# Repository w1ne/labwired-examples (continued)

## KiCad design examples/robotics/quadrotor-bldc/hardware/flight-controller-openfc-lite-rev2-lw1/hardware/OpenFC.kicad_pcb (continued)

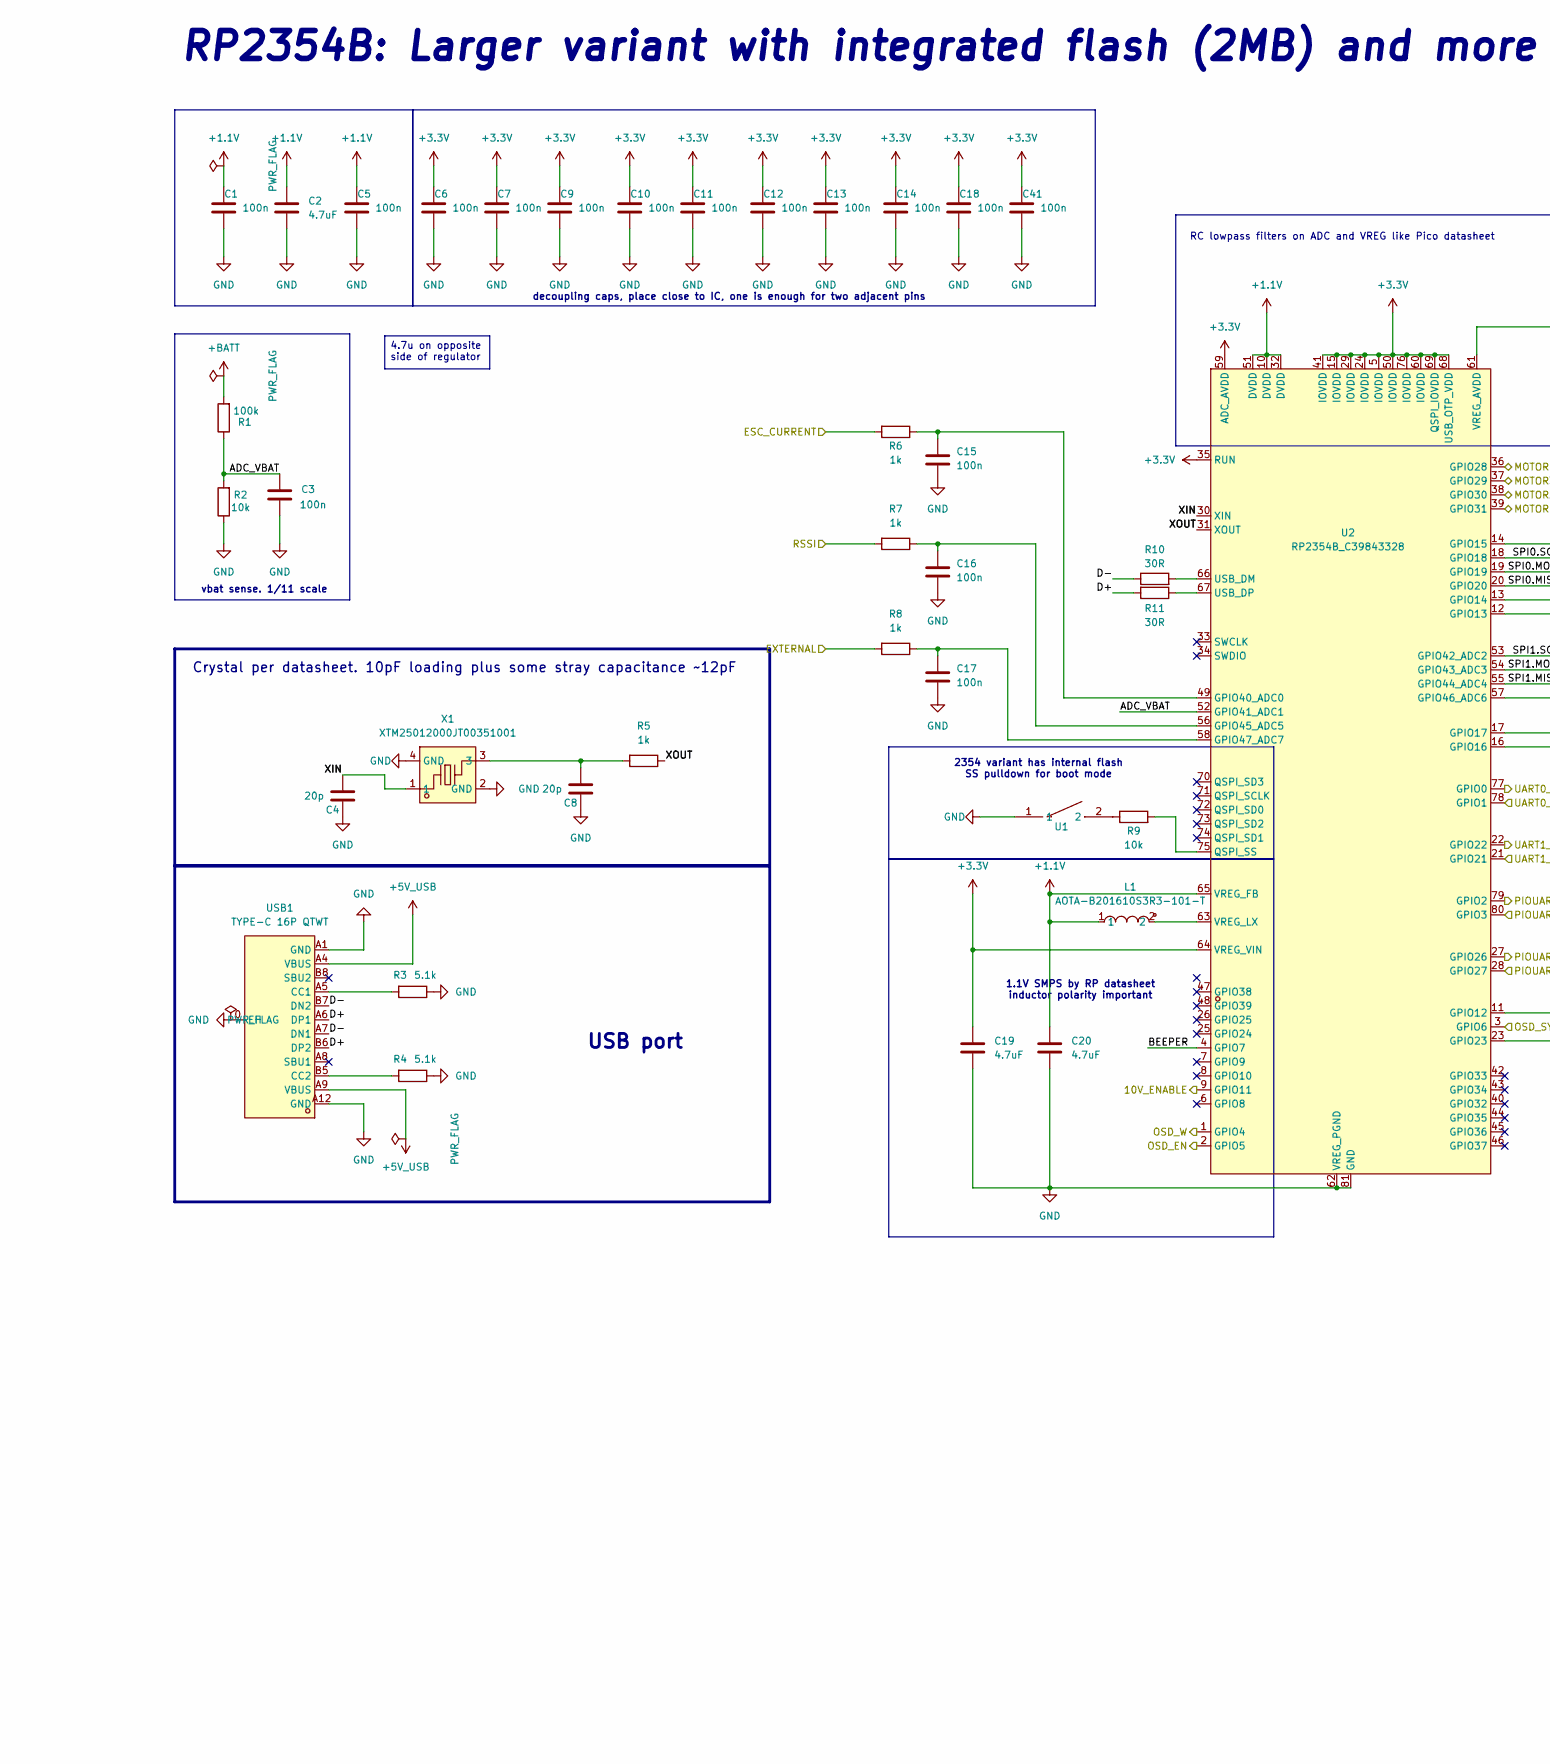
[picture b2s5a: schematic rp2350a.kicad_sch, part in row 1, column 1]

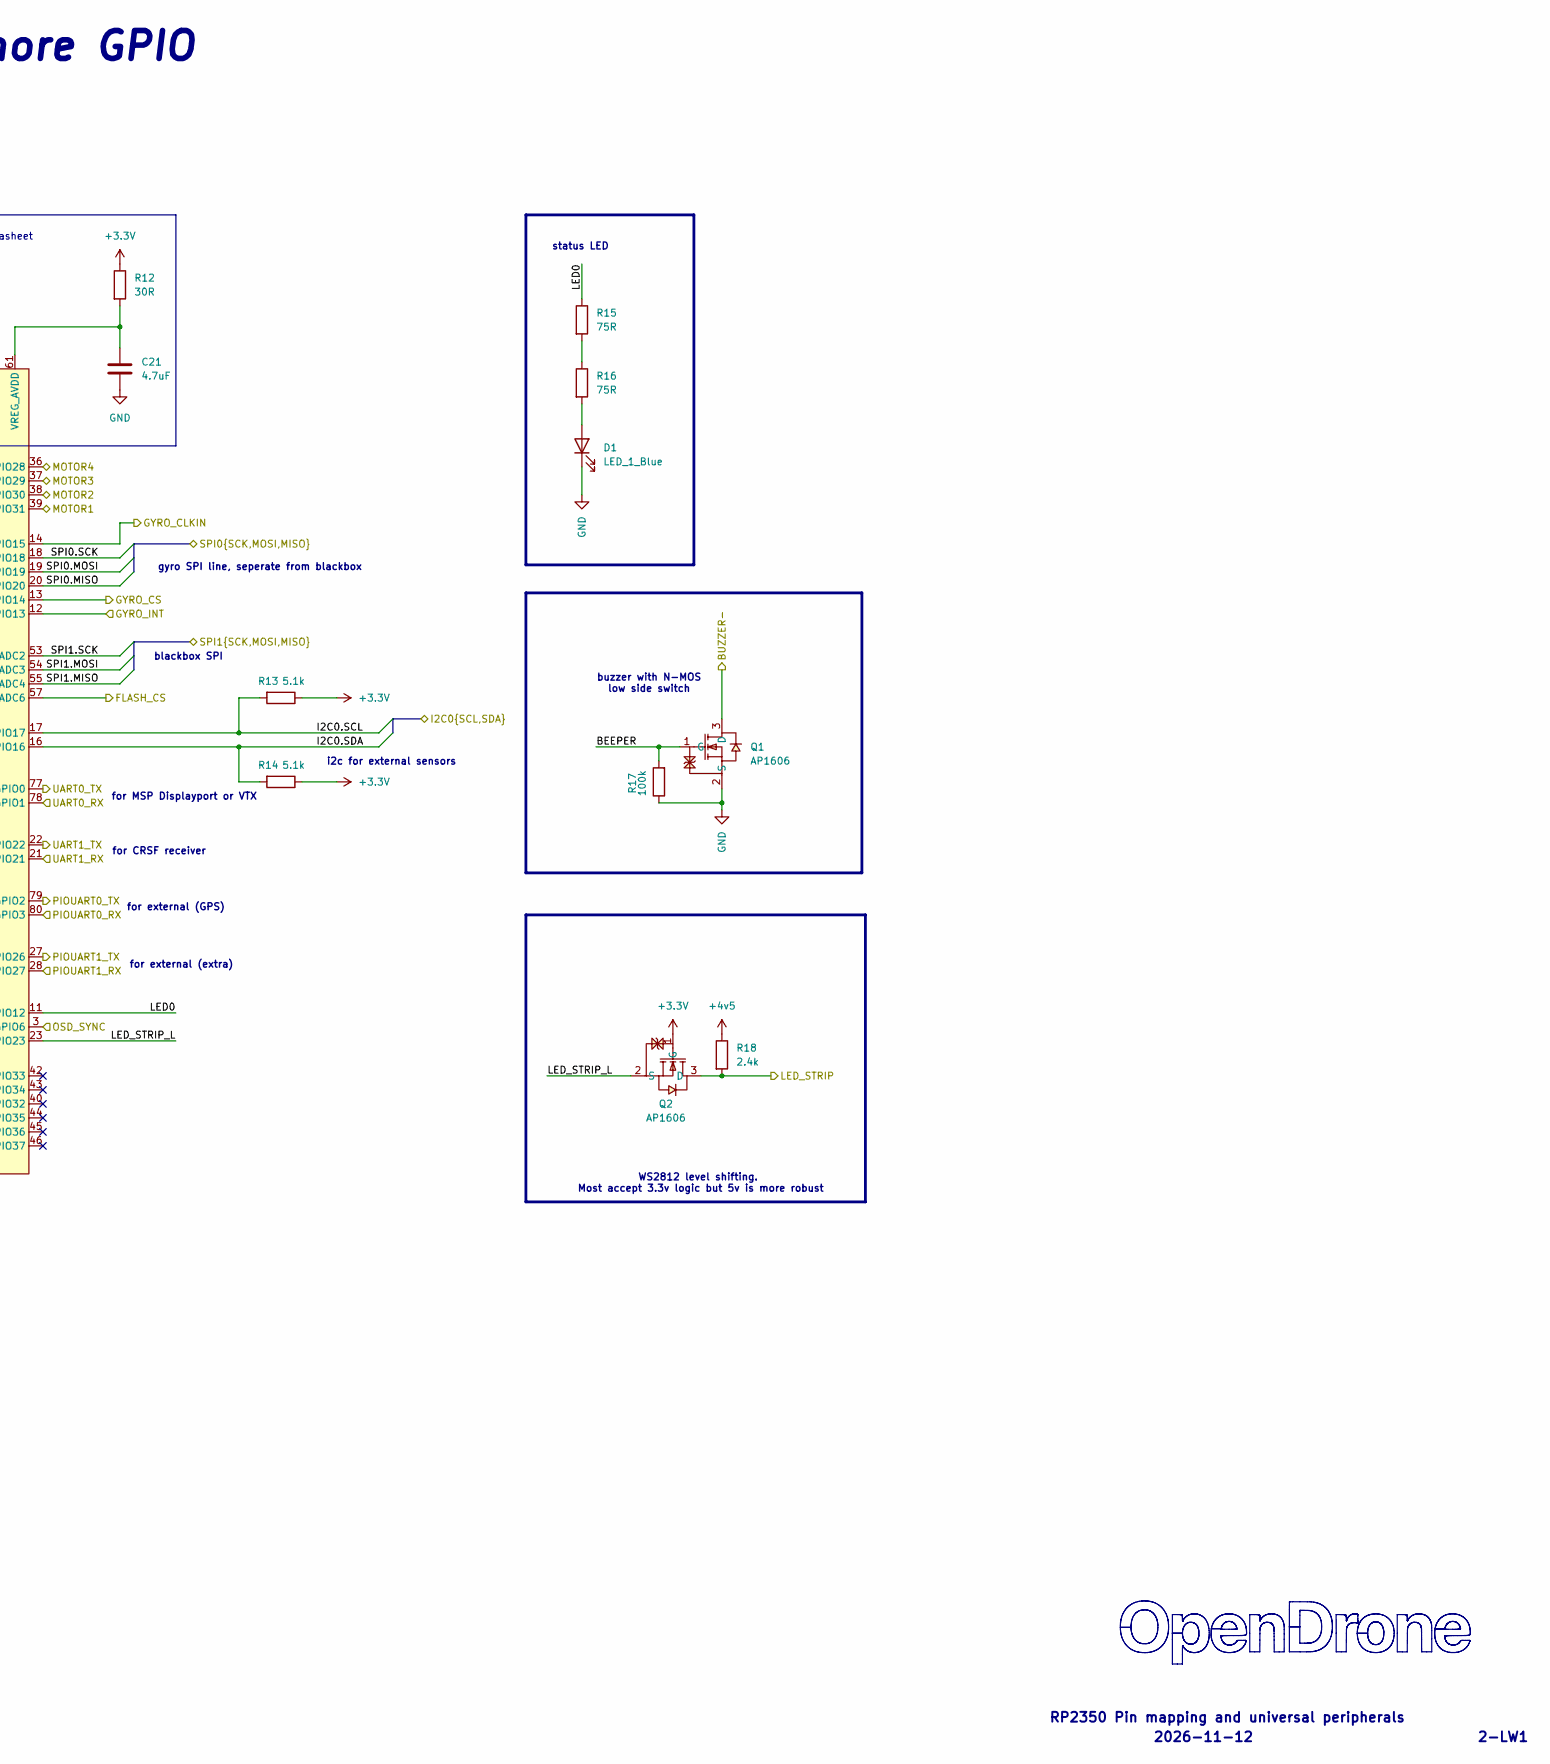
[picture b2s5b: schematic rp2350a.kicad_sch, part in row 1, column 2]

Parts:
C1, C3, C5, C6, C7, C9, C10, C11, C12, C13, C14, C15, C16, C17, C18, C41: 100n; C_0201_0603Metric; MPN GRM033R61E104KE14D; LCSC C76939
C2, C19, C20, C21: 4.7uF; C_0402_1005Metric; MPN CL05A475MP5NRNC; LCSC C23733
C4, C8: 20p; C_0201_0603Metric; MPN GRM0335C1H200JA01D; LCSC C76923
D1: LED_1_Blue; LED_0402_1005Metric; MPN XL-1005UBC; LCSC C22355736
L1: AOTA-B201610S3R3-101-T; IND-SMD_L2.0-W1.6_AOTA-B201610S3R3-101-T; MPN AOTA-B201610S3R3-101-T; LCSC C42411119
Q1, Q2: AP1606; DFN-3L_L1.0-W0.6-P0.65-BR; MPN AP1606; LCSC C2849580
R1, R17: 100k; R_0201_0603Metric; MPN 0201WMF1003TEE; LCSC C270364
R2, R9: 10k; R_0201_0603Metric; MPN RC0201FR-0710KL; LCSC C106225
R3, R4, R13, R14: 5.1k; R_0201_0603Metric; MPN 0201WMF5101TEE; LCSC C270344
R5, R6, R7, R8: 1k; R_0201_0603Metric; MPN 0201WMF1001TEE; LCSC C270365
R10, R11, R12: 30R; R_0201_0603Metric; MPN NQ01WMJ0300TEE; LCSC C778391
R15, R16: 75R; R_0201_0603Metric; MPN RC0201FR-0775RL; LCSC C274878
R18: 2.4k; R_0201_0603Metric; MPN RTT012401FTH; LCSC C166281
U1: TS2306A 240GF MSM 9_C2976675; SW-SMD_4P-L3.0-W2.0-P0.85-LS3.5; MPN TS2306A 240gf MSM 9; LCSC C2976675
U2: RP2354B_C39843328; QFN-80_L10.0-W10.0-P0.40-TL-EP3.4; MPN RP2354B; LCSC C39843328
USB1: TYPE-C 16P QTWT; USB-TYPE-C-SMD_TYPE-C-16P-QTWT; MPN TYPE-C 16P QTWT; LCSC C5187472
X1: XTM25012000JT00351001; CRYSTAL-SMD_4P-L2.5-W2.0-BL-A; MPN XTM25012000JT00351001; LCSC C37635340

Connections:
+1.1V: C1.1, C2.1, C5.1, C20.1, L1.1, U2.10 (DVDD), U2.32 (DVDD), U2.51 (DVDD), U2.65 (VREG_FB)
+3.3V: C6.1, C7.1, C9.1, C10.1, C11.1, C12.1, C13.1, C14.1, C18.1, C19.1, C41.1, Q2.1 (G), R12.1, R13.1, R14.1, U2.5 (IOVDD), U2.15 (IOVDD), U2.24 (IOVDD), U2.29 (IOVDD), U2.35 (RUN), U2.41 (IOVDD), U2.50 (IOVDD), U2.59 (ADC_AVDD), U2.60 (IOVDD), U2.64 (VREG_VIN), U2.68 (USB_OTP_VDD), U2.69 (QSPI_IOVDD), U2.76 (IOVDD); also elsewhere on the board
+4v5: R18.1; also elsewhere on the board
+5V_USB: USB1.A4 (VBUS), USB1.A9 (VBUS); also elsewhere on the board
+BATT: R1.2; also elsewhere on the board
/BLACKBOX/FLASH_CS: U2.57 (GPIO46_ADC6); also elsewhere on the board
/BLACKBOX/SPI1.MISO: U2.55 (GPIO44_ADC4); also elsewhere on the board
/BLACKBOX/SPI1.MOSI: U2.54 (GPIO43_ADC3); also elsewhere on the board
/BLACKBOX/SPI1.SCK: U2.53 (GPIO42_ADC2); also elsewhere on the board
/IMU/CLKIN: U2.14 (GPIO15); also elsewhere on the board
/IMU/CS: U2.13 (GPIO14); also elsewhere on the board
/IMU/GYRO_INT: U2.12 (GPIO13); also elsewhere on the board
/IMU/SPI0.MISO: U2.20 (GPIO20); also elsewhere on the board
/IMU/SPI0.MOSI: U2.19 (GPIO19); also elsewhere on the board
/IMU/SPI0.SCK: U2.18 (GPIO18); also elsewhere on the board
/OSD/OSD_EN: U2.2 (GPIO5); also elsewhere on the board
/OSD/OSD_SYNC: U2.3 (GPIO6); also elsewhere on the board
/OSD/OSD_W: U2.1 (GPIO4); also elsewhere on the board
/PADS/ADC2: R8.2; also elsewhere on the board
/PADS/BUZZER-: Q1.3 (D); also elsewhere on the board
/PADS/CURRENT: R6.2; also elsewhere on the board
/PADS/I2C0.SCL: R13.2, U2.17 (GPIO17); also elsewhere on the board
/PADS/I2C0.SDA: R14.2, U2.16 (GPIO16); also elsewhere on the board
/PADS/LED_STRIP: Q2.3 (D), R18.2; also elsewhere on the board
/PADS/M1: U2.39 (GPIO31); also elsewhere on the board
/PADS/M2: U2.38 (GPIO30); also elsewhere on the board
/PADS/M3: U2.37 (GPIO29); also elsewhere on the board
/PADS/M4: U2.36 (GPIO28); also elsewhere on the board
/PADS/PIOUART0_RX: U2.80 (GPIO3); also elsewhere on the board
/PADS/PIOUART0_TX: U2.79 (GPIO2); also elsewhere on the board
/PADS/PIOUART1_RX: U2.28 (GPIO27); also elsewhere on the board
/PADS/PIOUART1_TX: U2.27 (GPIO26); also elsewhere on the board
/PADS/RSSI: R7.2; also elsewhere on the board
/PADS/UART0_RX: U2.78 (GPIO1); also elsewhere on the board
/PADS/UART0_TX: U2.77 (GPIO0); also elsewhere on the board
/PADS/UART1_RX: U2.21 (GPIO21); also elsewhere on the board
/PADS/UART1_TX: U2.22 (GPIO22); also elsewhere on the board
/POWER/10V_ENABLE: U2.9 (GPIO11); also elsewhere on the board
/RP2350A/ADC_VBAT: C3.2, R1.1, R2.2, U2.52 (GPIO41_ADC1)
/RP2350A/BEEPER: Q1.1 (G), R17.2, U2.4 (GPIO7)
/RP2350A/D+: R11.2, USB1.A6 (DP1), USB1.B6 (DP2)
/RP2350A/D-: R10.1, USB1.A7 (DN1), USB1.B7 (DN2)
/RP2350A/LED0: R15.1, U2.11 (GPIO12)
/RP2350A/LED_STRIP_L: Q2.2 (S), U2.23 (GPIO23)
/RP2350A/XIN: C4.2, U2.30 (XIN), X1.1
/RP2350A/XOUT: R5.1, U2.31 (XOUT)
GND: C1.2, C2.2, C3.1, C4.1, C5.2, C6.2, C7.2, C8.1, C9.2, C10.2, C11.2, C12.2, C13.2, C14.2, C15.2, C16.2, C17.2, C18.2, C19.2, C20.2, C21.2, C41.2, D1.1 (K), Q1.2 (S), R2.1, R3.1, R4.1, R17.1, U1.1, U2.62 (VREG_PGND), U2.81 (GND), USB1.0 (EH), USB1.A1 (GND), USB1.A12 (GND), X1.2 (GND), X1.4 (GND); also elsewhere on the board
unnamed: C8.2, R5.2, X1.3
unnamed: D1.2 (A), R16.2
unnamed: R9.1, U1.2
unnamed: R15.2, R16.1
unnamed: C15.1, R6.1, U2.49 (GPIO40_ADC0)
unnamed: C16.1, R7.1, U2.56 (GPIO45_ADC5)
unnamed: C17.1, R8.1, U2.58 (GPIO47_ADC7)
unnamed: R9.2, U2.75 (QSPI_SS)
unnamed: R10.2, U2.66 (USB_DM)
unnamed: R11.1, U2.67 (USB_DP)
unnamed: C21.1, R12.2, U2.61 (VREG_AVDD)
unnamed: L1.2, U2.63 (VREG_LX)
unnamed: R3.2, USB1.A5 (CC1)
unnamed: R4.2, USB1.B5 (CC2)

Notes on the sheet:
RP2350 Pin mapping and universal peripherals
vbat sense. 1/11 scale
RP2354B: Larger variant with integrated flash (2MB) and more GPIO
blackbox SPI
2026-11-12
for MSP Displayport or VTX
2354 variant has internal flash SS pulldown for boot mode
for CRSF receiver
gyro SPI line, seperate from blackbox
decoupling caps, place close to IC, one is enough for two adjacent pins
for external (extra)
Crystal per datasheet. 10pF loading plus some stray capacitance ~12pF
for external (GPS)
i2c for external sensors
WS2812 level shifting. Most accept 3.3v logic but 5v is more robust
2-LW1
status LED
RC lowpass filters on ADC and VREG like Pico datasheet
USB port
1.1V SMPS by RP datasheet inductor polarity important
buzzer with N-MOS low side switch
4.7u on opposite side of regulator

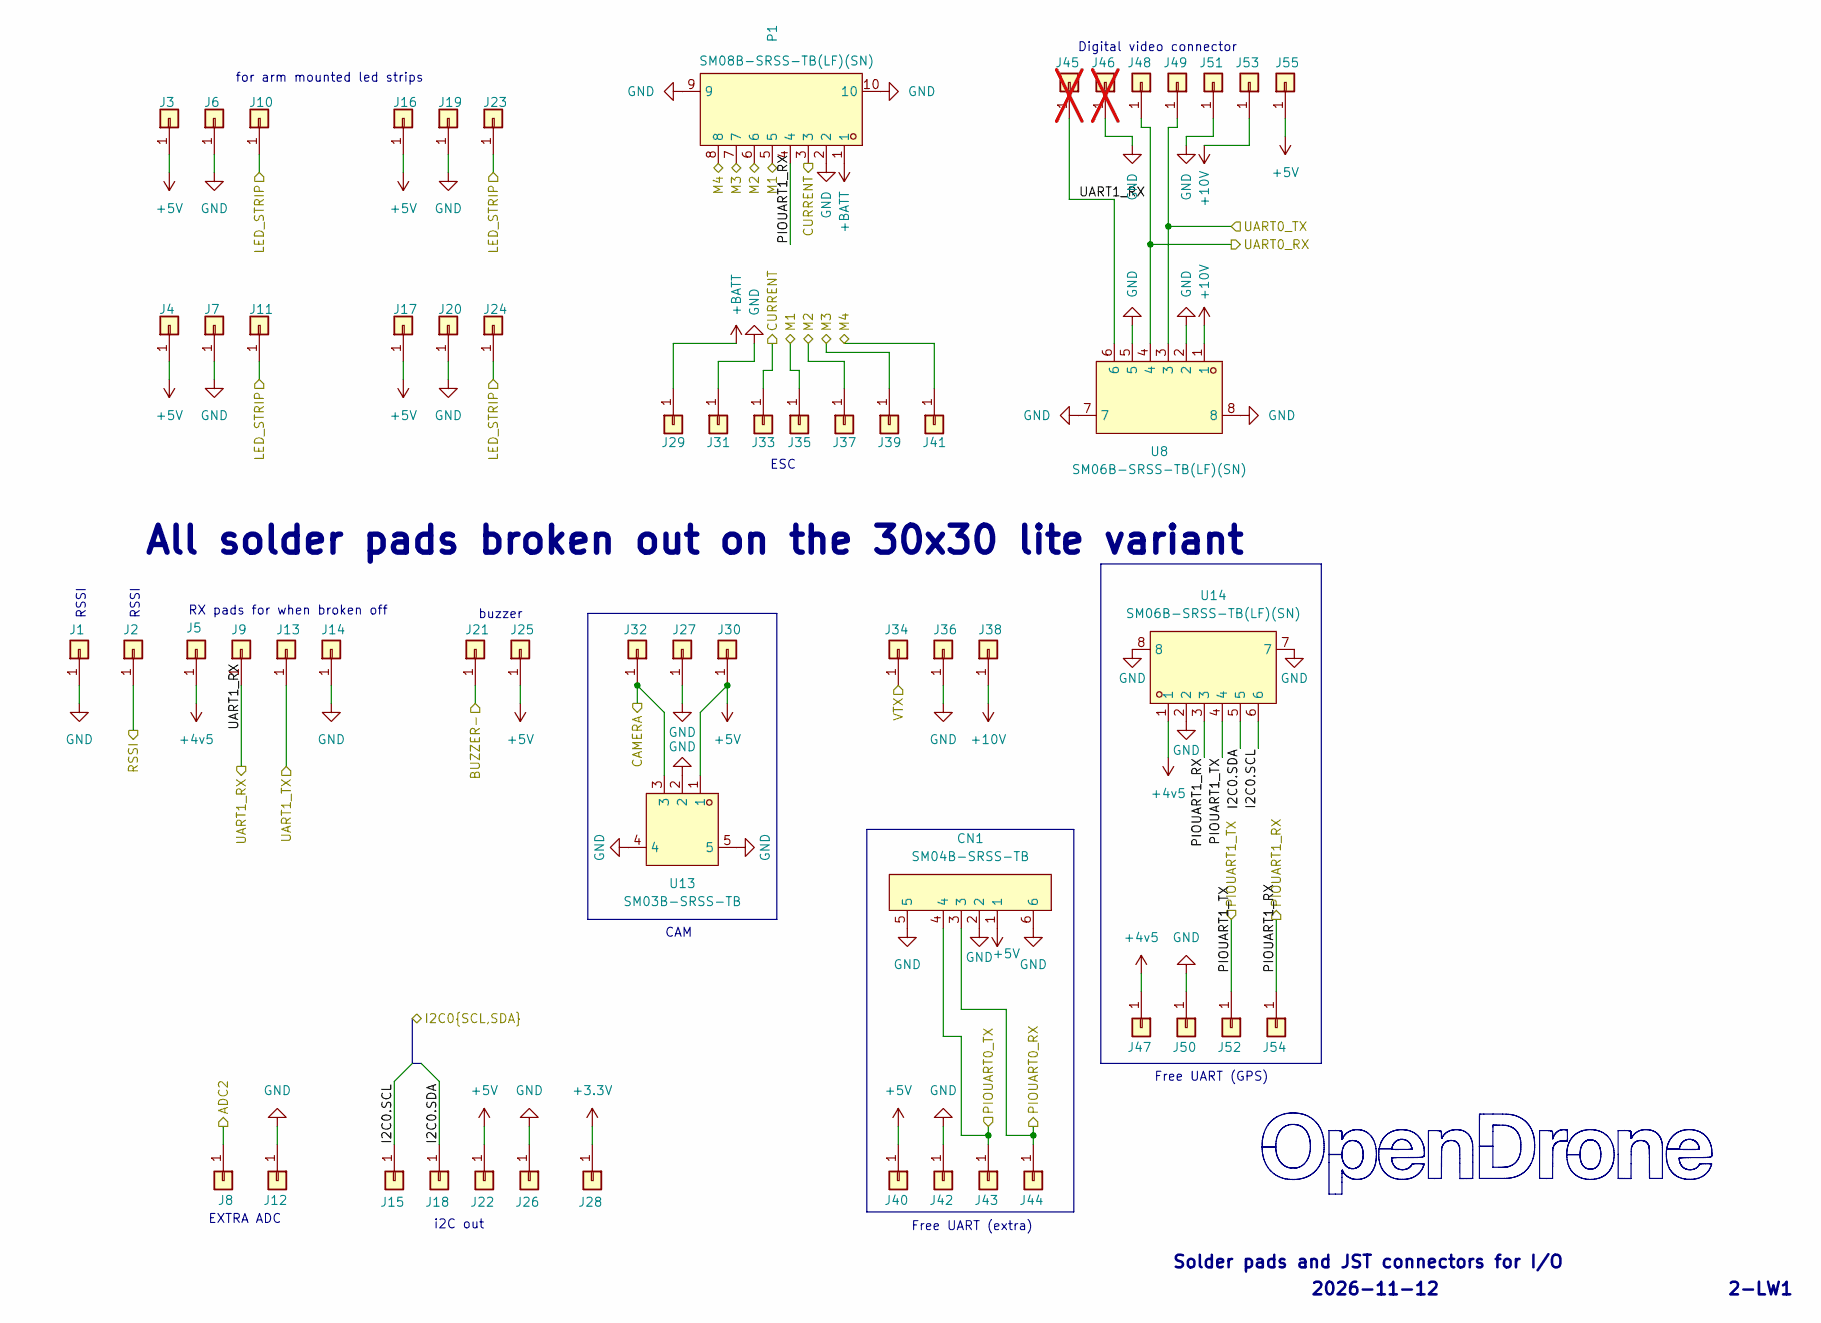
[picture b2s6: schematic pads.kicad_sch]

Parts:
CN1: SM04B-SRSS-TB; CONN-SMD_4P-P1.00_SM04B-SRSS-TB-LF-SN; MPN SM04B-SRSS-TB(LF)(SN); LCSC C160404
J1, J2, J3, J4, J5, J6, J7, J8, J9, J10, J11, J12, J13, J14, J15, J16, J17, J18, J19, J20, J21, J22, J23, J24, J25, J26, J27, J28, J29, J30, J31, J32, J33, J34, J35, J36, J37, J38, J39, J40, J41, J42, J43, J44, J47, J50, J53, J55: 5V; small_pad
J45, J46: 5V; small_pad; not fitted
J48: UART0_RX; small_pad
J49: UART0_TX; small_pad
J51: GND; small_pad
J52: 5V; SolderPad_1mm_J52
J54: 5V; SolderPad_1mm_J54
P1: SM08B-SRSS-TB(LF)(SN); CONN-TH_SM08B-SRSS-TB-LF-SN; MPN SM08B-SRSS-TB(LF)(SN); LCSC C160407
U8, U14: SM06B-SRSS-TB(LF)(SN); CONN-SMD_SM06B-SRSS-TB-LF-SN; MPN SM06B-SRSS-TB(LF)(SN); LCSC C160405
U13: SM03B-SRSS-TB; CONN-SMD_SM03B-SRSS-TB-LF-SN-P; MPN SM03B-SRSS-TB(LF)(SN); LCSC C160403

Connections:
+3.3V: J28.1; also elsewhere on the board
+4v5: J5.1, J47.1, U14.1; also elsewhere on the board
+5V: CN1.1, J3.1, J4.1, J16.1, J17.1, J22.1, J25.1, J30.1, J40.1, J55.1, U13.1; also elsewhere on the board
+10V: J38.1, J53.1, U8.1; also elsewhere on the board
+BATT: J29.1, P1.1; also elsewhere on the board
/OSD/VIDEO_IN: J32.1, U13.3; also elsewhere on the board
/OSD/VIDEO_OUT: J34.1; also elsewhere on the board
/PADS/ADC2: J8.1; also elsewhere on the board
/PADS/BUZZER-: J21.1; also elsewhere on the board
/PADS/CURRENT: J33.1, P1.3; also elsewhere on the board
/PADS/I2C0.SCL: J15.1, U14.6; also elsewhere on the board
/PADS/I2C0.SDA: J18.1, U14.5; also elsewhere on the board
/PADS/LED_STRIP: J10.1, J11.1, J23.1, J24.1; also elsewhere on the board
/PADS/M1: J35.1, P1.5; also elsewhere on the board
/PADS/M2: J37.1, P1.6; also elsewhere on the board
/PADS/M3: J39.1, P1.7; also elsewhere on the board
/PADS/M4: J41.1, P1.8; also elsewhere on the board
/PADS/PIOUART0_RX: CN1.3, J44.1; also elsewhere on the board
/PADS/PIOUART0_TX: CN1.4, J43.1; also elsewhere on the board
/PADS/PIOUART1_RX: J54.1, P1.4, U14.3; also elsewhere on the board
/PADS/PIOUART1_TX: J52.1, U14.4; also elsewhere on the board
/PADS/RSSI: J2.1; also elsewhere on the board
/PADS/UART0_RX: J48.1, U8.4; also elsewhere on the board
/PADS/UART0_TX: J49.1, U8.3; also elsewhere on the board
/PADS/UART1_RX: J9.1, J45.1, U8.6; also elsewhere on the board
/PADS/UART1_TX: J13.1; also elsewhere on the board
GND: CN1.2, CN1.5, CN1.6, J1.1, J6.1, J7.1, J12.1, J14.1, J19.1, J20.1, J26.1, J27.1, J31.1, J36.1, J42.1, J46.1, J50.1, J51.1, P1.2, P1.9, P1.10, U8.2, U8.5, U8.7, U8.8, U13.2, U13.4, U13.5, U14.2, U14.7, U14.8; also elsewhere on the board

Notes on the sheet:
2026-11-12
RSSI
Free UART (extra)
Solder pads and JST connectors for I/O
i2C out
CAM
All solder pads broken out on the 30x30 lite variant
Free UART (GPS)
buzzer
2-LW1
RX pads for when broken off
ESC
Digital video connector
EXTRA ADC
for arm mounted led strips

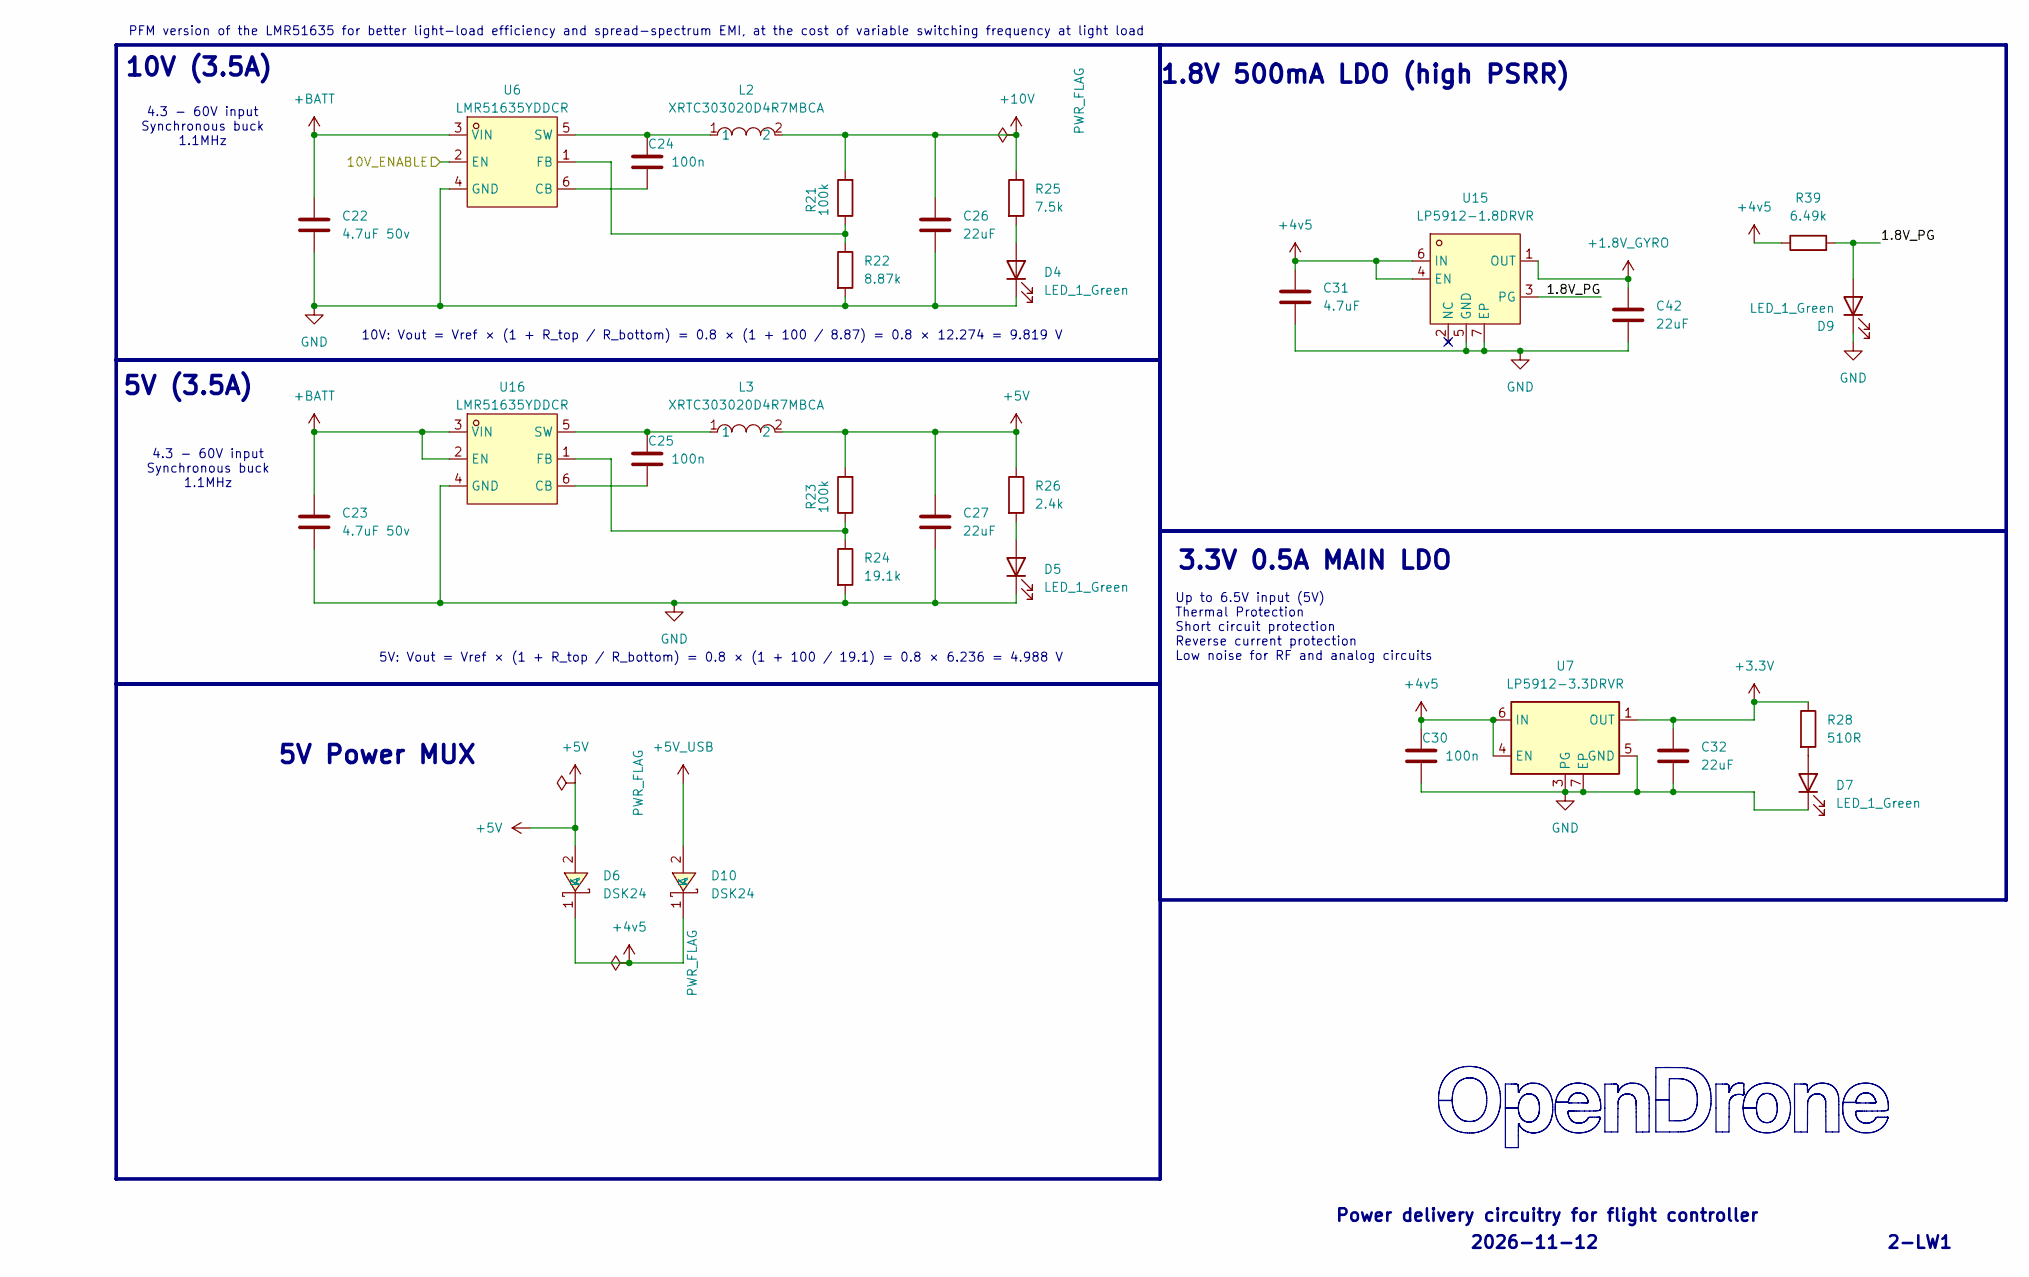
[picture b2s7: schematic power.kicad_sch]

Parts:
C22, C23: 4.7uF 50v; C_0805_2012Metric; MPN CL21A475KBQNNNE; LCSC C98192
C24, C25, C30: 100n; C_0201_0603Metric; MPN GRM033R61E104KE14D; LCSC C76939
C26, C27: 22uF; C_0603_1608Metric; MPN CL10A226MO7JZNC; LCSC C2762594
C31: 4.7uF; C_0402_1005Metric; MPN CL05A475MP5NRNC; LCSC C23733
C32: 22uF; C_0402_1005Metric; MPN CL05A226MQ5QUNC; LCSC C105226
C42: 22uF; C_0402_1005Metric; MPN GRM155R60J226ME11D; LCSC C415703
D4, D5, D7, D9: LED_1_Green; LED_0402_1005Metric; MPN XL-1005UGC; LCSC C965793
D6, D10: DSK24; SOD-123_L2.8-W1.8-LS3.7-RD; MPN DSK24; LCSC C64890
L2, L3: XRTC303020D4R7MBCA; IND-SMD_L3.0-W3.0_AFE303020S; MPN XRTC303020D4R7MBCA; LCSC C39846837
R21, R23: 100k; R_0201_0603Metric; MPN 0201WMF1003TEE; LCSC C270364
R22: 8.87k; R_0201_0603Metric; MPN RTT018871FTH; LCSC C332577
R24: 19.1k; R_0201_0603Metric; MPN RC-01W1912FT; LCSC C320741
R25: 7.5k; R_0201_0603Metric; MPN RC0201FR-077K5L; LCSC C474437
R26: 2.4k; R_0201_0603Metric; MPN RTT012401FTH; LCSC C166281
R28: 510R; R_0201_0603Metric; MPN RC0201FR-07510RL; LCSC C57784
R39: 6.49k; R_0201_0603Metric; MPN AF0201FR-076K49L; LCSC C2107920
U6, U16: LMR51635YDDCR; SOT-23-6_L2.9-W1.6-P0.95-LS2.8-BL; MPN LMR51635YDDCR; LCSC C45262770
U7: LP5912-3.3DRVR; WSON-6-1EP_2x2mm_P0.65mm_EP1x1.6mm; MPN LP5912-3.3DRVR; LCSC C524780
U15: LP5912-1.8DRVR; WSON-6-1EP_2x2mm_P0.65mm_EP1x1.6mm_ThermalVias; MPN LP5912-1.8DRVR; LCSC C2876234

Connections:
+1.8V_GYRO: C42.1, U15.1 (OUT); also elsewhere on the board
+3.3V: C32.1, R28.1, U7.1 (OUT); also elsewhere on the board
+4v5: C30.1, C31.1, D6.1 (K), D10.1 (K), R39.1, U7.4 (EN), U7.6 (IN), U15.4 (EN), U15.6 (IN); also elsewhere on the board
+5V: C27.1, D6.2 (A), L3.2, R23.2, R26.1; also elsewhere on the board
+5V_USB: D10.2 (A); also elsewhere on the board
+10V: C26.1, L2.2, R21.2, R25.1; also elsewhere on the board
+BATT: C22.1, C23.1, U6.3 (VIN), U16.2 (EN), U16.3 (VIN); also elsewhere on the board
/POWER/1.8V_PG: D9.2 (A), R39.2, U15.3 (PG)
/POWER/10V_ENABLE: U6.2 (EN); also elsewhere on the board
GND: C22.2, C23.2, C26.2, C27.2, C30.2, C31.2, C32.2, C42.2, D4.1 (K), D5.1 (K), D7.1 (K), D9.1 (K), R22.2, R24.2, U6.4 (GND), U7.3 (PG), U7.5 (GND), U7.7 (EP), U15.5 (GND), U15.7 (EP), U16.4 (GND); also elsewhere on the board
unnamed: D4.2 (A), R25.2
unnamed: D5.2 (A), R26.2
unnamed: D7.2 (A), R28.2
unnamed: C24.2, U6.6 (CB)
unnamed: R21.1, R22.1, U6.1 (FB)
unnamed: C24.1, L2.1, U6.5 (SW)
unnamed: C25.2, U16.6 (CB)
unnamed: R23.1, R24.1, U16.1 (FB)
unnamed: C25.1, L3.1, U16.5 (SW)

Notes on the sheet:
5V Power MUX
4.3 - 60V input Synchronous buck 1.1MHz
Power delivery circuitry for flight controller
2026-11-12
2-LW1
10V: Vout = Vref × (1 + R_top / R_bottom) = 0.8 × (1 + 100 / 8.87) = 0.8 × 12.274 = 9.819 V
5V: Vout = Vref × (1 + R_top / R_bottom) = 0.8 × (1 + 100 / 19.1) = 0.8 × 6.236 = 4.988 V
Up to 6.5V input (5V) Thermal Protection Short circuit protection Reverse current protection Low noise for RF and analog circuits
5V (3.5A)
1.8V 500mA LDO (high PSRR)
PFM version of the LMR51635 for better light-load efficiency and spread-spectrum EMI, at the cost of variable switching frequency at light load
10V (3.5A)
3.3V 0.5A MAIN LDO

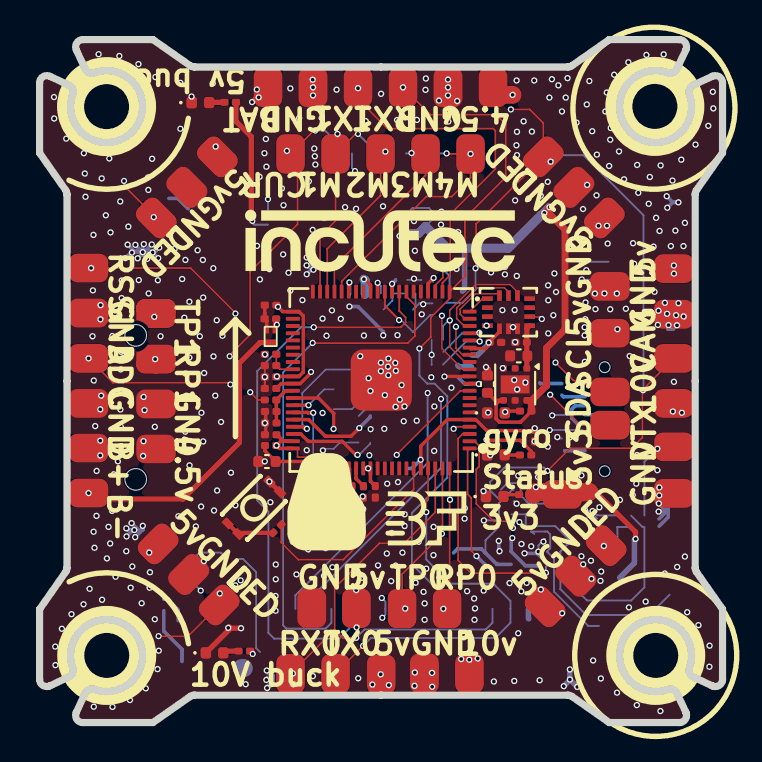
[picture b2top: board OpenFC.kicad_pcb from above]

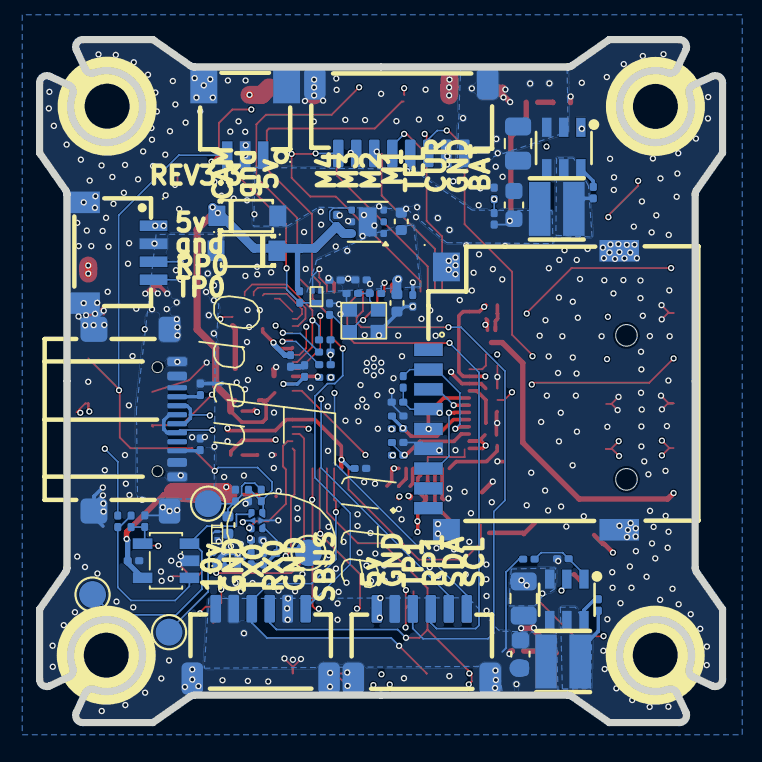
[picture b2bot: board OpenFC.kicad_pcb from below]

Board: 6 copper layers, 37.9 x 37.9 mm, 164 parts (72 on the bottom side), 82 nets.

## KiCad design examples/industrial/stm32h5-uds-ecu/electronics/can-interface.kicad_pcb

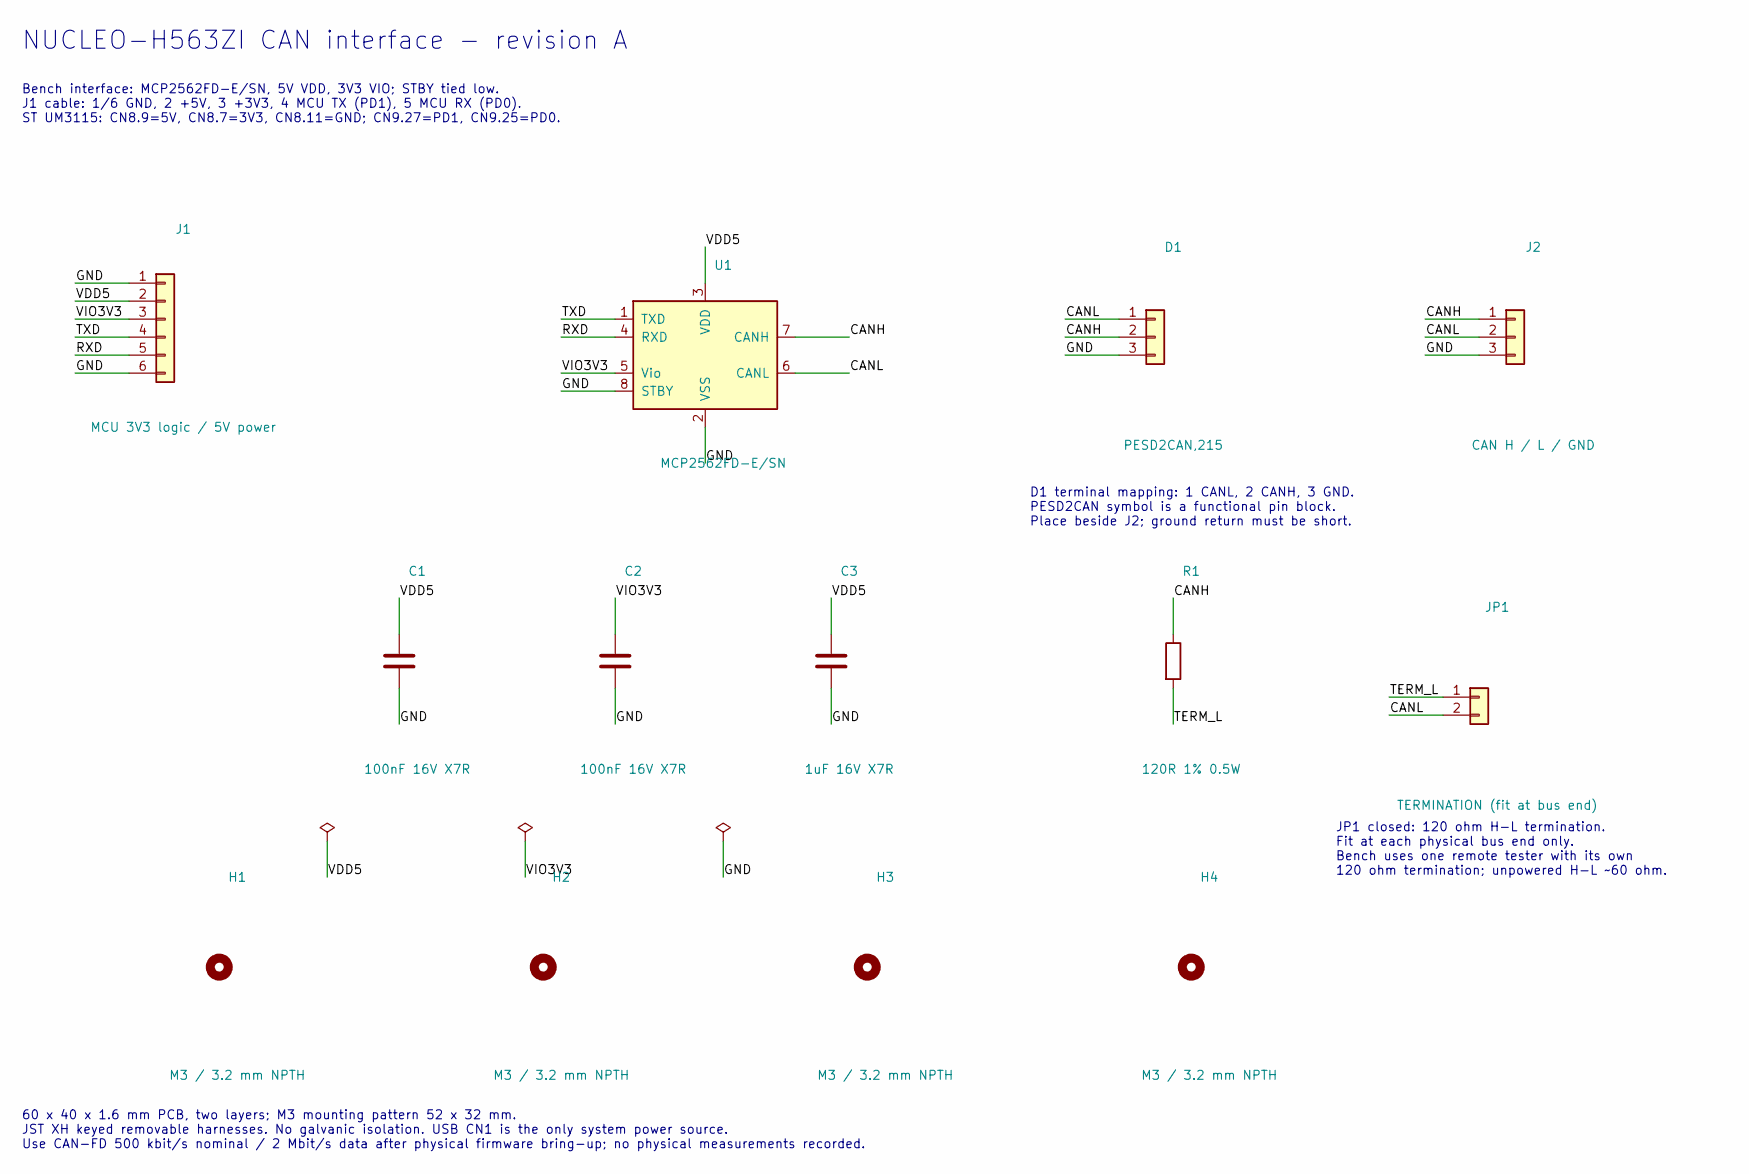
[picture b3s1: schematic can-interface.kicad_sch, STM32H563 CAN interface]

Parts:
C1, C2: 100nF 16V X7R; C; MPN GRM188R71C104KA01D
C3: 1uF 16V X7R; C; MPN GRM188R71C105KA12D
D1: PESD2CAN,215; ESD; MPN PESD2CAN,215
H1, H2, H3, H4: M3 / 3.2 mm NPTH; MountingHole
J1: MCU 3V3 logic / 5V power; MCU6; MPN B6B-XH-A(LF)(SN)
J2: CAN H / L / GND; CAN3; MPN B3B-XH-A(LF)(SN)
JP1: TERMINATION (fit at bus end); TERM2; MPN TSW-102-07-G-S
R1: 120R 1% 0.5W; R; MPN ERJ-P08F1200V
U1: MCP2562FD-E/SN; U; MPN MCP2562FD-E/SN

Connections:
/CANH: D1.2, J2.1, R1.1, U1.7 (CANH)
/CANL: D1.1, J2.2, JP1.2, U1.6 (CANL)
/GND: C1.2, C2.2, C3.2, D1.3, J1.1, J1.6, J2.3, U1.2 (VSS), U1.8 (STBY)
/RXD: J1.5, U1.4 (RXD)
/TERM_L: JP1.1, R1.2
/TXD: J1.4, U1.1 (TXD)
/VDD5: C1.1, C3.1, J1.2, U1.3 (VDD)
/VIO3V3: C2.1, J1.3, U1.5 (Vio)

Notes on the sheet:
NUCLEO-H563ZI CAN interface - revision A
Bench interface: MCP2562FD-E/SN, 5V VDD, 3V3 VIO; STBY tied low. J1 cable: 1/6 GND, 2 +5V, 3 +3V3, 4 MCU TX (PD1), 5 MCU RX (PD0). ST UM3115: CN8.9=5V, CN8.7=3V3, CN8.11=GND; CN9.27=PD1, CN9.25=PD0.
D1 terminal mapping: 1 CANL, 2 CANH, 3 GND. PESD2CAN symbol is a functional pin block. Place beside J2; ground return must be short.
JP1 closed: 120 ohm H-L termination. Fit at each physical bus end only. Bench uses one remote tester with its own 120 ohm termination; unpowered H-L ~60 ohm.
60 x 40 x 1.6 mm PCB, two layers; M3 mounting pattern 52 x 32 mm. JST XH keyed removable harnesses. No galvanic isolation. USB CN1 is the only system power source. Use CAN-FD 500 kbit/s nominal / 2 Mbit/s data after physical firmware bring-up; no physical measurements recorded.

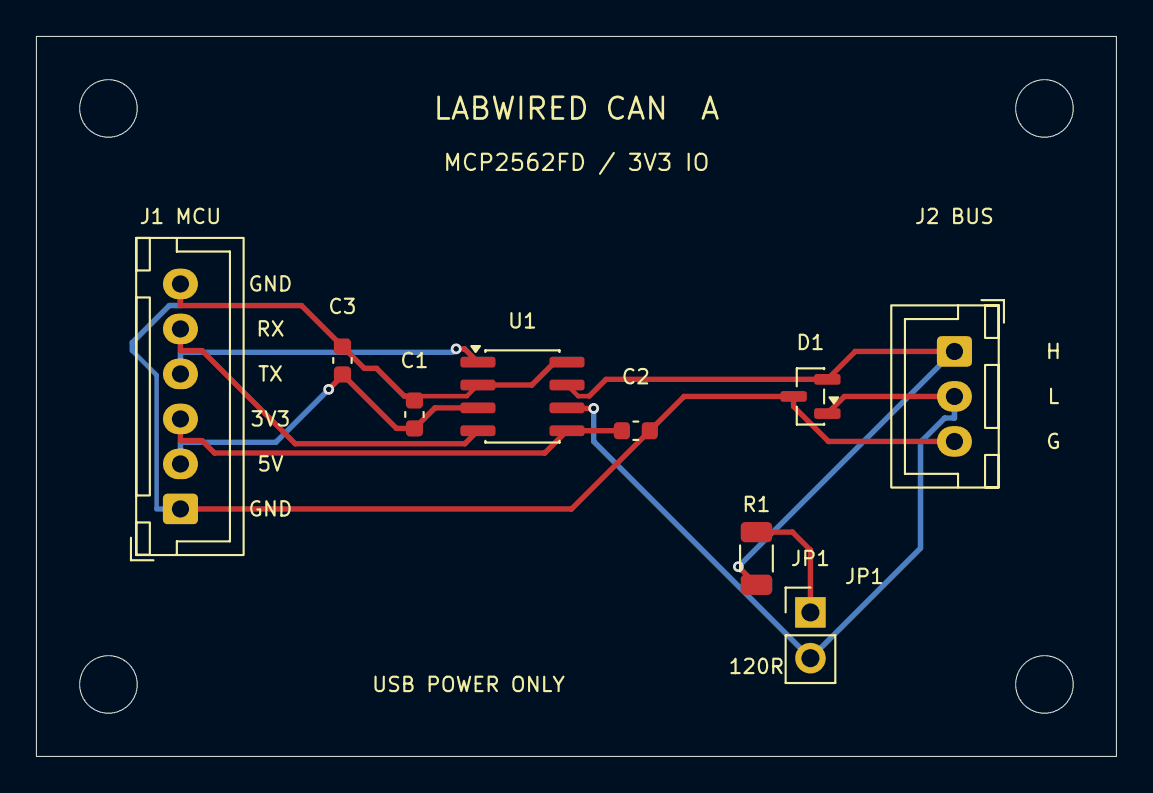
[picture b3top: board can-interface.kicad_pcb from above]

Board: 2 copper layers, 60.0 x 40.0 mm, 13 parts (0 on the bottom side), 8 nets.
